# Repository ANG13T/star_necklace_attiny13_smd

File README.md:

# ATtiny13 SMD Star Wearable 
This star-shaped blinky wearable showcases mesmerizing constellation and star art, brought to life by the bright programmable LEDs showcasing dazzling light patterns on a sleek SMD PCB canvas. Powered by the ATtiny13 IC, this wearable features ICSP pins at the bottom, allowing for quick programmability. With the aid of a stencil, if needed, users can hone their SMD soldering skills while assembling this board 🌟.

## Features
- 0603 SMD LED Blinky 💡
- Programmable ICSP Pins 💻
- Constellation Silk Screen Art 🌌
- Star-shaped Edge Cut ⭐️

## Schematic

## PCB Layout

## PCB Preview 

## Components and BOM
- [Coin Cell Battery Holder](https://www.amazon.com/Hxchen-BS-6DIP-Electrical-Lithium-Battery/dp/B07VZCXQJ3/ref=sr_1_4?crid=137ZLMXB341HN&dib=eyJ2IjoiMSJ9.FAZfUVjx-amvVZQFDQayx1DTAELAT7UHsjt1i3umGrmq6VrMWubXK4cR3pBM2OXSFJxGxn66Rqdb75hRqESjyekIWibwSGPvcUW_ZunogmkfUMXzrjglRcwq7rYWKGZNgoAJeeKDEVF0zIDRyL6-7NgC4t-UccmiJd2TyywsCXh8i3oRKWlyLkxmMmLMCbIMxj1R2Xmxx2ad2woiqsd3-W30hNI-EFuWxWSaqX6obgs.yfpnrf9w42S0wzco9R1xrDe15wqjDZEtSnvYh6hZCOk&dib_tag=se&keywords=smd+3v+coin+battery+holder&qid=1711984515&sprefix=sm3v+coin+battery+holder%2Caps%2C280&sr=8-4): $7.99
- [3V Coin Cell Battery](https://www.amazon.com/LiCB-CR2032-Lithium-Battery-10-Pack/dp/B071D4DKTZ/ref=sr_1_7?crid=1S3G5YBWB3BRE&dib=eyJ2IjoiMSJ9.bDz2iaX_geo6C_G1I5ucCSGZaYp8caqzjiwddTfxVtc8_8tHbLnVF8rMzk-mkwg04mJ6obyYIqQGZUpACYCZ5lnXn9nGypEf45t46hUi6eEiFvew0RbMfK0udv3dqnUhkzPikNvxi4gPwBEiMHdZ8e-exyI2_pzWSlyBi4cYkWVYXd51sT2QrJZKuUqhofcd4u3LqAC1kbJyYZh5DqHmLS8Sxh_mMKrYphv7fQRuspyrfA6JVP1bw9beFWpZHGH9drfXg6IiSUj4L9D32pNFpSFs5o7dPN2TV0icnrw3qKA.Rmmm3N3AgkriWudaT8TdFe4-ypdy_AJakXMsLmsvbZ4&dib_tag=se&keywords=3v+coin+battery&qid=1711984455&sprefix=3v+coin+%2Caps%2C224&sr=8-7): $5.99
- [SPDT Slide Switch](https://www.amazon.com/HiLetgo-SS-12D00-Toggle-Switch-Vertical/dp/B07RTJDW27/ref=sr_1_4?crid=YSA37ZYTWJQM&dib=eyJ2IjoiMSJ9.PYS6HCski7gW11Gq-UAeSQj8SBHSzD180cI1nbGWcXK7Dp06lM6zqNPosuPfLqegQ29oD6GP43aZ2oQ7HufjJKxJoQa29J9V1qqDfY7xrDITYNDThTADT1Gb7MJ1lGHxxEUfLo0-HmNX2Pw2aps1ZDC2OouDXuql8rgg_iSnBk5f96bTT1qDLb5LiIe8LEK_J7a_p7IdSRM-xkNgEVdadux_Ph7K5sw5lQGPgPY9WUo.D57jUh1Qg1oihDNW_TS585ED9jITCtneSdJriPzYjFE&dib_tag=se&keywords=SPDT+Slide+Switch&qid=1711984557&sprefix=smd+3v+coin+battery+holder%2Caps%2C217&sr=8-4): $5.39
- [ICSP Header Pins](https://www.amazon.com/HiLetgo-20pcs-2-54mm-Single-Header/dp/B07R5QDL8D/ref=sr_1_1?crid=1ZI2WW0K1UVV1&dib=eyJ2IjoiMSJ9.Z03ljbfhyANmY1ei8JGMUZUuJhL7NIIz_sZfPmKCuuLMyPUidCW-W9ajkEJF_-4pGROeiR-EtswTIiK2-ENCvRDHStqMNh12OQEc-WsApX7tPj7BYr7RSHcZZPjcr9f0ezhpHCnXm648DM0qyWu4A2P6OAJ4Rvr6yMPrdsgtjU87Y_L3_9ZwKS2zViIR4PV9gIL0GEzgfPFof8N3aM8QEzWb3Am2GmZUarzgZFB3xbU.jlylI_o6_j4RsvPgvDTgjY2OJimpUz3He-sX-1QYATA&dib_tag=se&keywords=ICSP+Header+Pins&qid=1711984579&sprefix=icsp+header+pins%2Caps%2C292&sr=8-1): $5.49
- [SMD Resistors 0805 100ohm](https://www.amazon.com/Chanzon-Resistor-Tolerance-Resistors-Certificated/dp/B08R8BQGDX/ref=sr_1_1?crid=2QWOKWJ1CDEL5&dib=eyJ2IjoiMSJ9.ToiECrG3n_2uZyigwZtzI8J7MhQvMvS8VHcOXC7XkwhH1J0il7JkUTf5TuG8hdQfaFJapTpRvc__abcBNFAz5X-FsRtf9XmJiJvJwj7dTdttk26BJ-Hj0eSJbBKojQqPfQV4nsT0fv59QTmZcYxsepVhHAg16B6FUEi9sf1mXKhwewYrRc3E3Zf-bXB7eNgQ4hNMWa02g8dSCsVN2A637lsm1wxFMzk4O7lvyictXZk.X3ACTPlfG_T_scdkahRXDIYvJ6CVPkZGUva2qDO3GlQ&dib_tag=se&keywords=smd+resistors+100+ohm+0805&qid=1711984634&sprefix=smd+resistors+100+ohm+080%2Caps%2C230&sr=8-1): $4.99
- [SMD Resistors 4.7k ohm](https://www.amazon.com/Chanzon-Resistor-Tolerance-Resistors-Certificated/dp/B08QRZ1G1G/ref=sr_1_2?crid=7I9SSIVUXIRZ&dib=eyJ2IjoiMSJ9.3CZdcymc-qiThgGRfNUB8F_TQmqcwSepIdKEFEAY1XsqFS2a2H41v19jo9u2rUbW7xouUYhGww-92dT4Gqus_bV1aSX8rysh9oNl4ZHJ77_vVT5p47ROKc0CnbmhRIVrkN_d31Ktt0PjPZwcP55Bqno9NEHC8cfiMzmMSAGaiv_09pXChsm3xTIZVWJ5JkH6seUbWGN11FDsTqIFYnCWcviKfURUIdvIJ5s8lJSpUr4.Md8Qn5V2-F0h6iX7uPnjq_uJzZ1tee6DTvgu3pD_BoE&dib_tag=se&keywords=smd+resistors+4.7k+ohm+0805&qid=1711984676&sprefix=smd+resistors+4.7k+ohm+0805%2Caps%2C208&sr=8-2): $5.99
- [SMD LEDs](https://www.amazon.com/Assorted-Lighting-Electronics-Components-Emitting/dp/B09XZNT471/ref=sr_1_3?crid=2ZWCQ9DTMCF4M&dib=eyJ2IjoiMSJ9.sDwHTS4D2DIKr3cdVtjfim0V7TpCzw4AF9EMmGS_if0eo9v_T1kMIaTbcPaoZbpMmKQgrFglZJdEecoMTXmCaykQepw33KVrEolM0VbhVevNEW7ypKZPOb9YhM2F7Q9KF5I-cWUAOdiSlqzJ5GHi6jEsOAC0zjzb-keFIm-UgsFV146o-BpqE8uHu2uMRfUqPCvLQdgTAYPdxIXvGlkYEsj8UzMMcJiEuazCPYKxiSQ.3DteHtKt1BeG-KHRvYo0YtbTwnB8TzS_kqCd1-G8oHg&dib_tag=se&keywords=0603+smd+led&qid=1711984402&sprefix=0603+smd+%2Caps%2C373&sr=8-3):  $7.99
- [ATtiny13A-SSU](https://www.aliexpress.us/item/3256805886404756.html?spm=a2g0o.productlist.main.11.739f7adc3zUVWt&algo_pvid=2c67ae99-56bd-4efd-a7cd-d74647ab97e4&algo_exp_id=2c67ae99-56bd-4efd-a7cd-d74647ab97e4-5&pdp_npi=4%40dis%21USD%214.73%214.73%21%21%214.73%214.73%21%402103237317119850009201244e5dc3%2112000035602944482%21sea%21US%210%21AB&curPageLogUid=LQ37zN2AT2KD&utparam-url=scene%3Asearch%7Cquery_from%3A): $4.73

## ATtiny13A Overview 
The ATtiny13A is a versatile and cheap microcontroller IC developed by Atmel. It belongs to the AVR family, which are known for their low power consumption and high performance.

#### ATtiny13 Characteristics

| Feature              | Description                                          |
|----------------------|------------------------------------------------------|
| Architecture         | AVR 8-bit RISC                                      |
| Flash Memory         | 1 KB                                                 |
| SRAM                 | 64 bytes                                             |
| EEPROM               | 64 bytes                                             |
| Clock Speed          | Up to 20 MHz                                         |
| Timers/Counters      | Two 8-bit with PWM capability                        |
| I/O Pins             | 6                                                    |
| Analog Comparator    | Included                                             |
| Power Saving Modes   | Idle, ADC Noise Reduction, Power-down                |
| Programming          | Atmel Studio, Arduino IDE, etc.                      |
| Packages             | PDIP, SOIC, etc.                                     |

## ATtiny13A Pin Out

Below is a preview pinout for the IC. 

The pinout breakdown is as follows:

| Pin  | Name | Description                                         |
|------|------|-----------------------------------------------------|
| 1    | SCK  | Serial Clock (SPI): Clock signal for SPI interface. |
| 2    | MISO | Master In Slave Out (SPI): Data input from SPI slave devices. |
| 3    | VCC  | Supply Voltage: Connect to the positive supply voltage (typically +5V). |
| 4    | GND  | Ground: Connect to the ground reference.            |
| 5    | MOSI | Master Out Slave In (SPI): Data output to SPI slave devices. |
| 6    | RST  | Reset: Reset signal, typically active low, used to reset the microcontroller. |

## Programming via Arduino Nano (ICSP)

## Contributing
If you would like to implement any design iterations to the PCB, please fork the repository and make a pull request with the features or fixes you want to implement.

## Support
If you enjoyed this project, please consider [becoming a sponsor](https://github.com/sponsors/ANG13T) or donating on [buymeacoffee](https://www.buymeacoffee.com/angelinatsuboi) in order to fund my future projects. 

To check out my other works, visit my [GitHub profile](https://github.com/ANG13T).

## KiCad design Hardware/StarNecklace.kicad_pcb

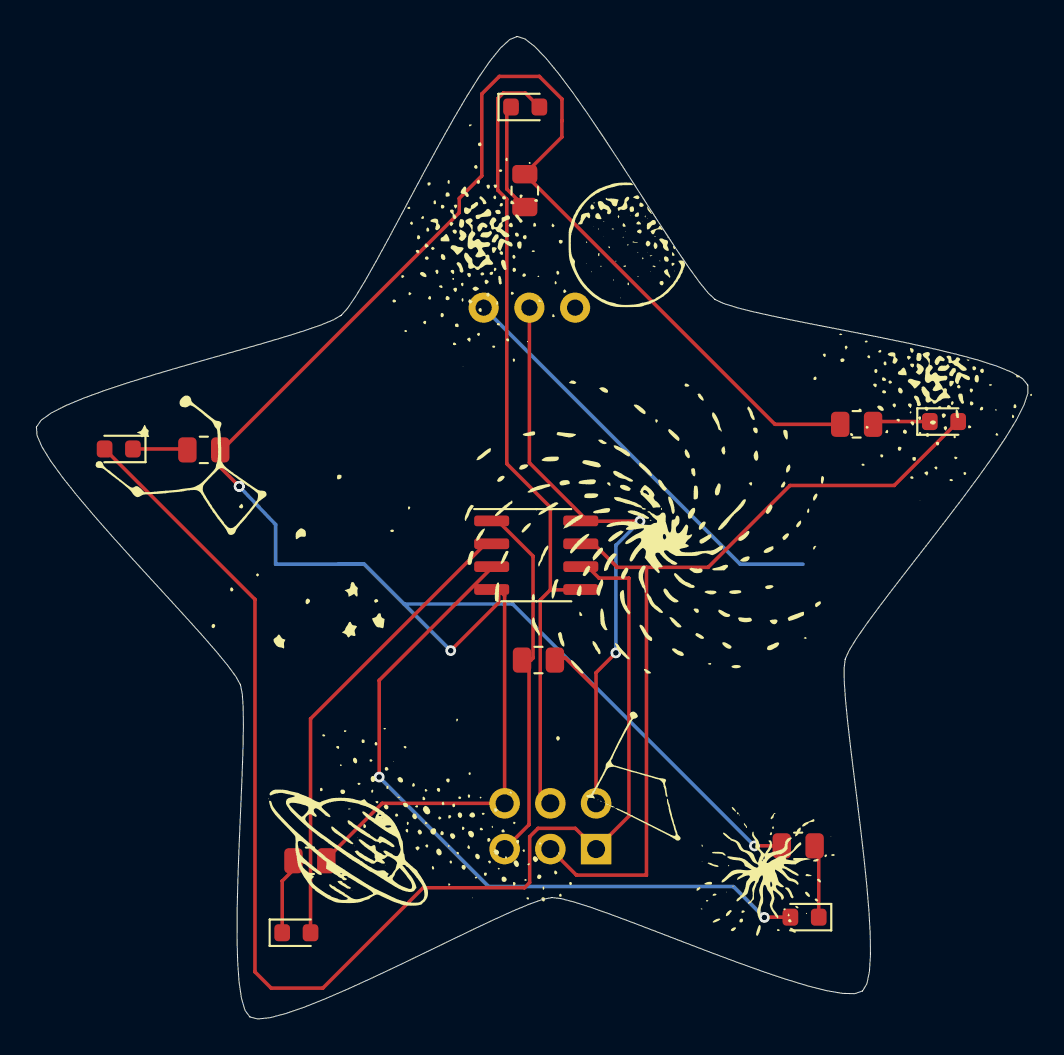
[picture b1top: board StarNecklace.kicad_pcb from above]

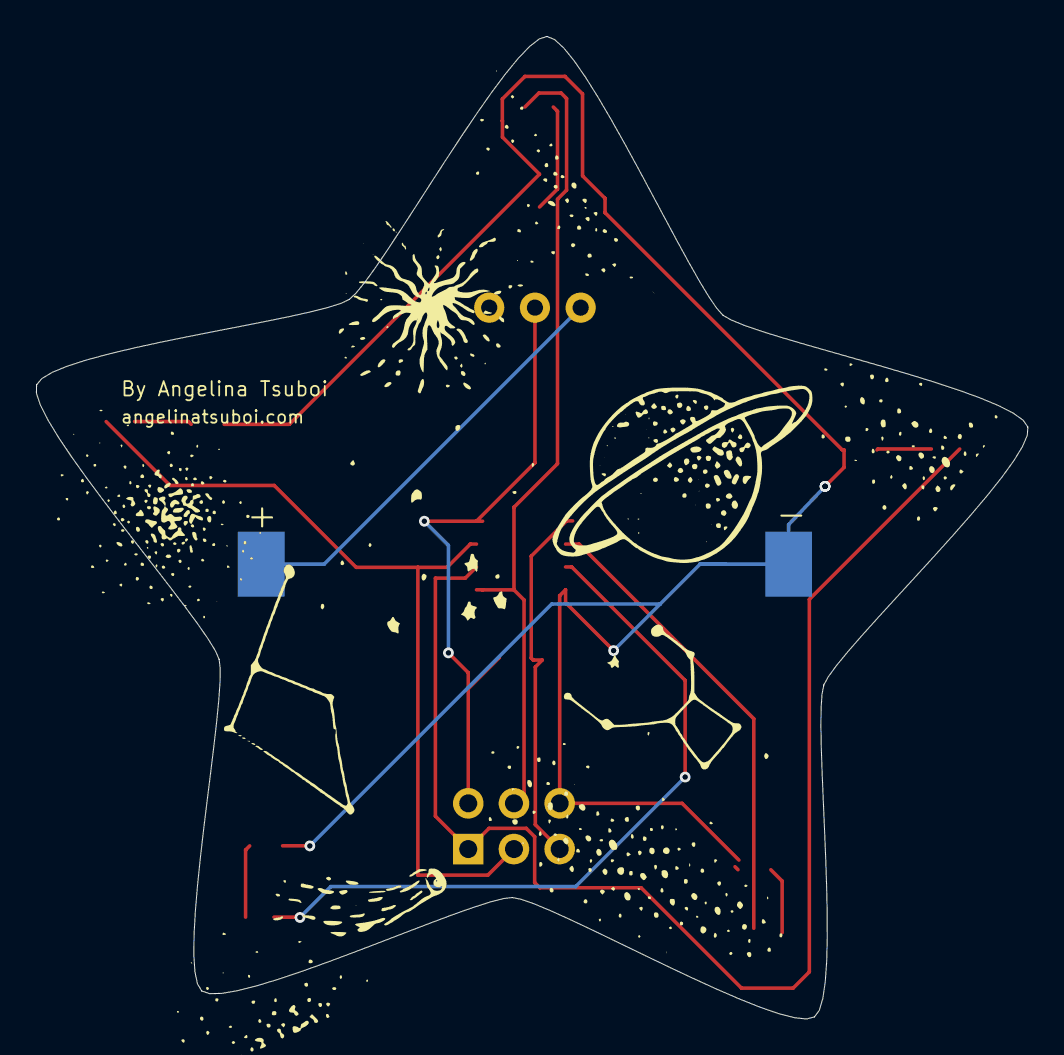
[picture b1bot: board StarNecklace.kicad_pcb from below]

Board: 2 copper layers, 55.1 x 54.6 mm, 15 parts (3 on the bottom side), 14 nets.

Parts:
BAT1: Coin Cell Holder 3V; BatteryHolder_Keystone_1060_1x2032
D1, D2, D3, D4, D5: LED; LED_0603_1608Metric
J1: Conn_02x03_Odd_Even; PinHeader_2x03_P2.54mm_Vertical
R1, R2, R3, R4, R5: 100; R_0805_2012Metric
R6: 4.7k; R_0805_2012Metric
SW1: SW_SPDT; Schiebeschalter_SS-12D00
U1: ATtiny13A; SOIC-8_3.9x4.9mm_P1.27mm

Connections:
GNDREF: BAT1.2 (-), J1.6, R1.2, R2.2, R3.2, R4.2, R5.2, U1.4 (GND)
MISO: D2.2 (A), J1.1, U1.6 (PB1)
MOSI: D1.2 (A), J1.4, U1.5 (PB0)
unnamed: BAT1.1 (+), SW1.3 (C)
unnamed: D1.1 (K), R1.1
unnamed: D2.1 (K), R2.1
unnamed: D3.1 (K), R3.1
unnamed: D4.1 (K), R4.1
unnamed: D5.1 (K), R5.1
PB3: D4.2 (A), U1.2 (PB3)
PB4: D5.2 (A), U1.3 (PB4)
RST: J1.5, R6.2, U1.1 (~RESET/PB5)
SCK: D3.2 (A), J1.3, U1.7 (PB2)
VCC: J1.2, R6.1, SW1.2 (B), U1.8 (VCC)

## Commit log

2024-03-22 feat: init sch
2024-03-22 feat: remove
2024-03-22 feat: init new sdh
2024-03-22 feat: init schematic
2024-03-23 feat: update footprints and init pcb
2024-03-27 feat: init routing
2024-03-28 feat: init silk art
2024-04-01 feat: commit design files
2024-04-01 feat: init gerbers
2024-04-01 feat: init images
